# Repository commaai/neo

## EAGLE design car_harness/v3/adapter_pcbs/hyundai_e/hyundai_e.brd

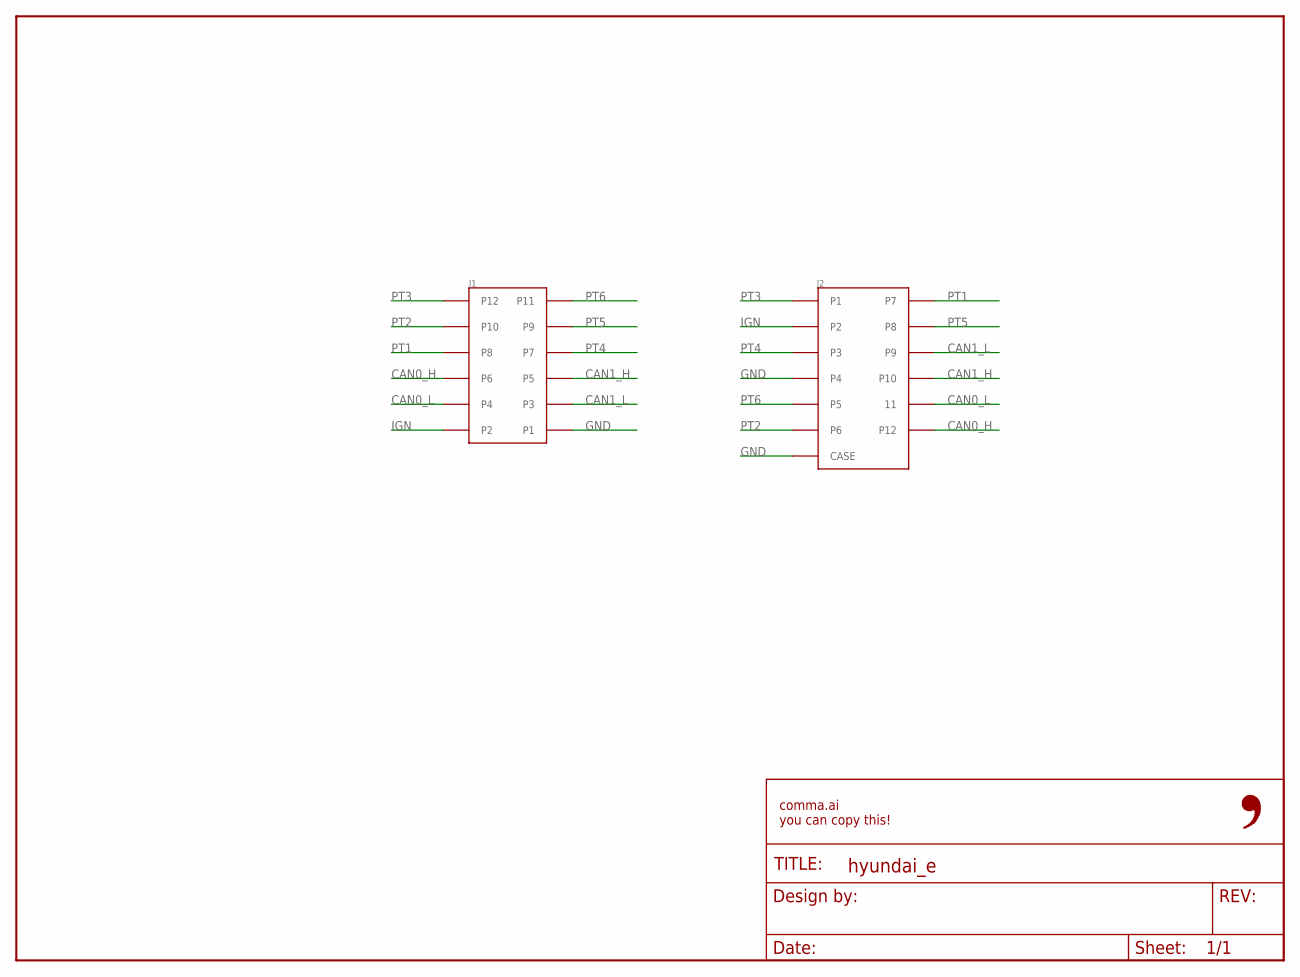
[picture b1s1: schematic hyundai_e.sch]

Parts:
FRAME1: FRAME-LETTER-OPENNO_PACKAGE; DUMMY
J1: 5018761240
J2: MG645845

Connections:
CAN0_H: J1.P6, J2.P12
CAN0_L: J1.P4, J2.P11 (11)
CAN1_H: J1.P5, J2.P10
CAN1_L: J1.P3, J2.P9
GND: J1.P1, J2.P4, J2.P$1 (CASE), J2.P$2 (CASE)
IGN: J1.P2, J2.P2
PT1: J1.P8, J2.P7
PT2: J1.P10, J2.P6
PT3: J1.P12, J2.P1
PT4: J1.P7, J2.P3
PT5: J1.P9, J2.P8
PT6: J1.P11, J2.P5

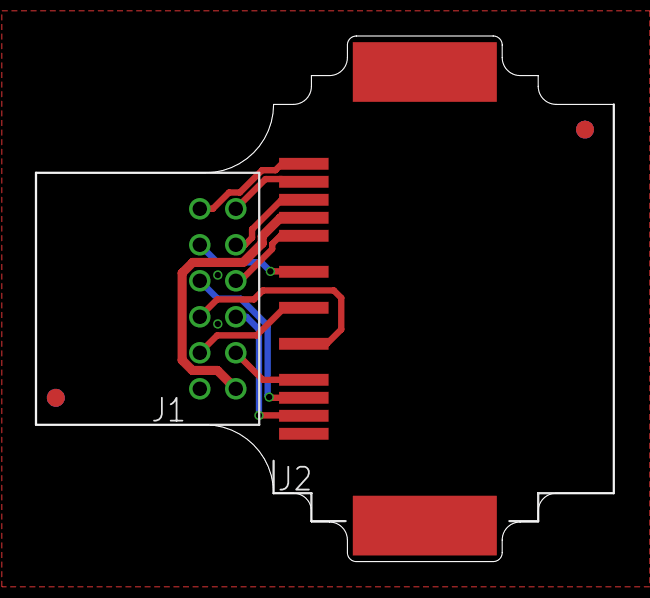
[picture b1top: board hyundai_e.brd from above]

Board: 2 copper layers, 32.1 x 29.2 mm, 6 parts (1 on the bottom side), 12 nets.

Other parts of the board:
U$1: LOGO
U$2, U$3: FIDUCIAL

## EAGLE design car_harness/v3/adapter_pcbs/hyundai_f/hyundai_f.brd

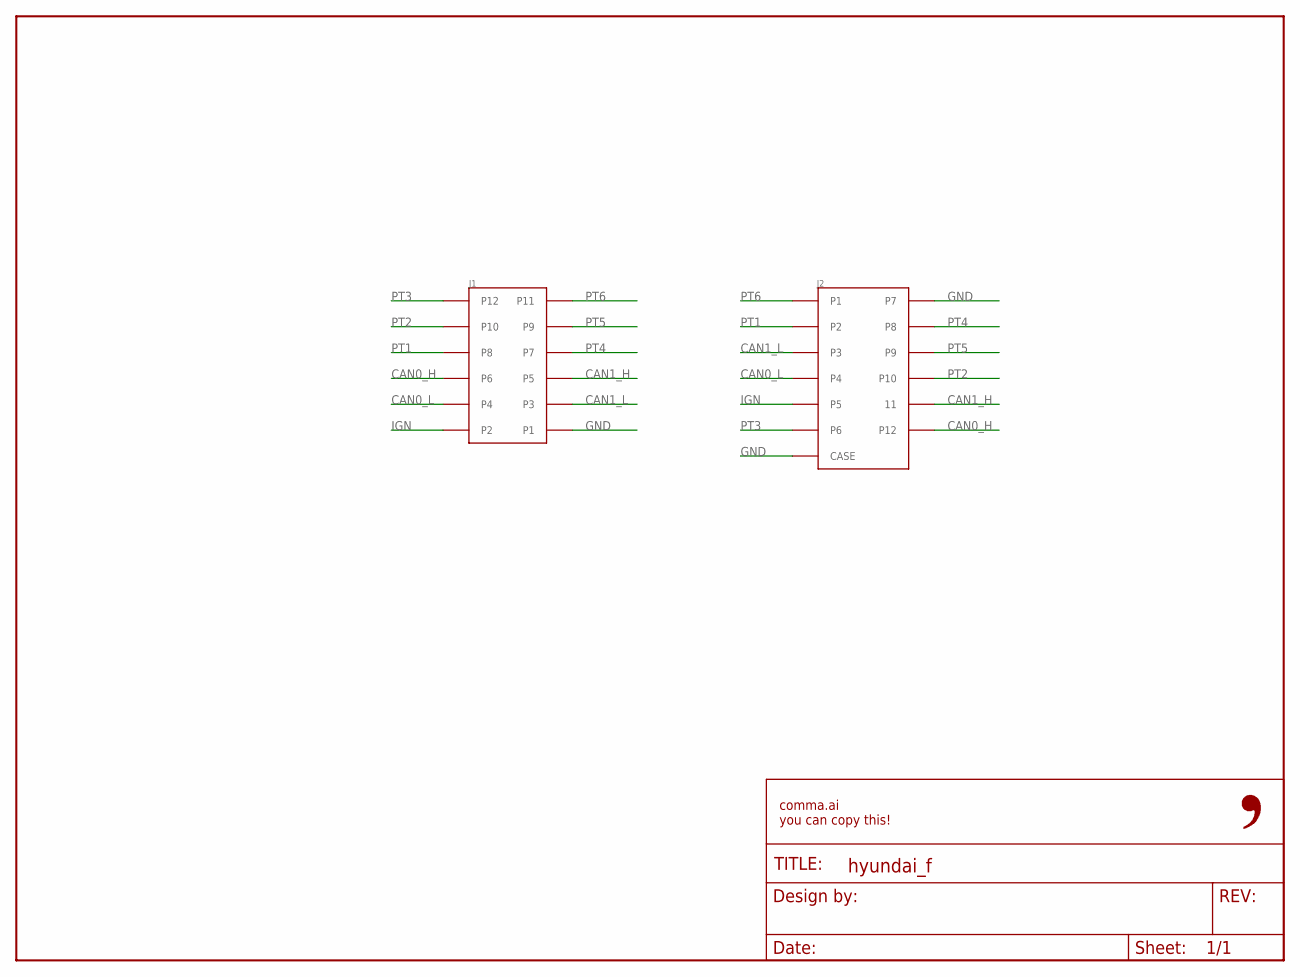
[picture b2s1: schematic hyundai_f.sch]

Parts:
FRAME1: FRAME-LETTER-OPENNO_PACKAGE; DUMMY
J1: 5018761240
J2: MG645845

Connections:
CAN0_H: J1.P6, J2.P12
CAN0_L: J1.P4, J2.P4
CAN1_H: J1.P5, J2.P11 (11)
CAN1_L: J1.P3, J2.P3
GND: J1.P1, J2.P7, J2.P$1 (CASE), J2.P$2 (CASE)
IGN: J1.P2, J2.P5
PT1: J1.P8, J2.P2
PT2: J1.P10, J2.P10
PT3: J1.P12, J2.P6
PT4: J1.P7, J2.P8
PT5: J1.P9, J2.P9
PT6: J1.P11, J2.P1

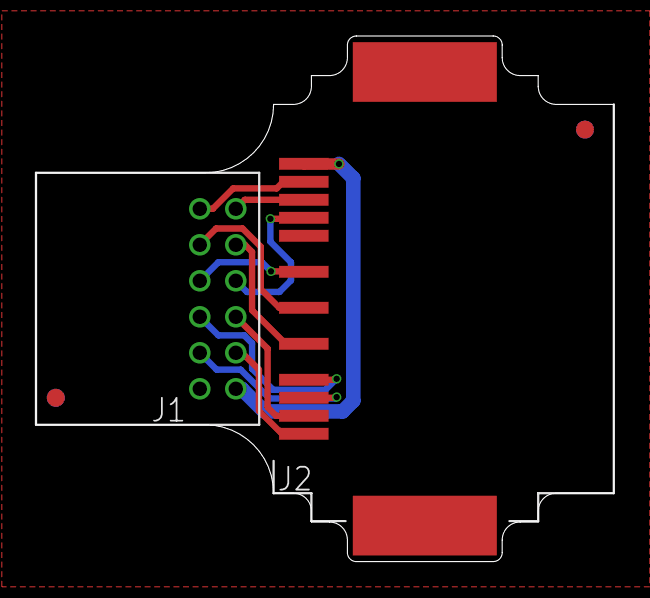
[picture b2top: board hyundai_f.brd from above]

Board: 2 copper layers, 32.1 x 29.2 mm, 6 parts (1 on the bottom side), 12 nets.

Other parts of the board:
U$1: LOGO
U$2, U$3: FIDUCIAL

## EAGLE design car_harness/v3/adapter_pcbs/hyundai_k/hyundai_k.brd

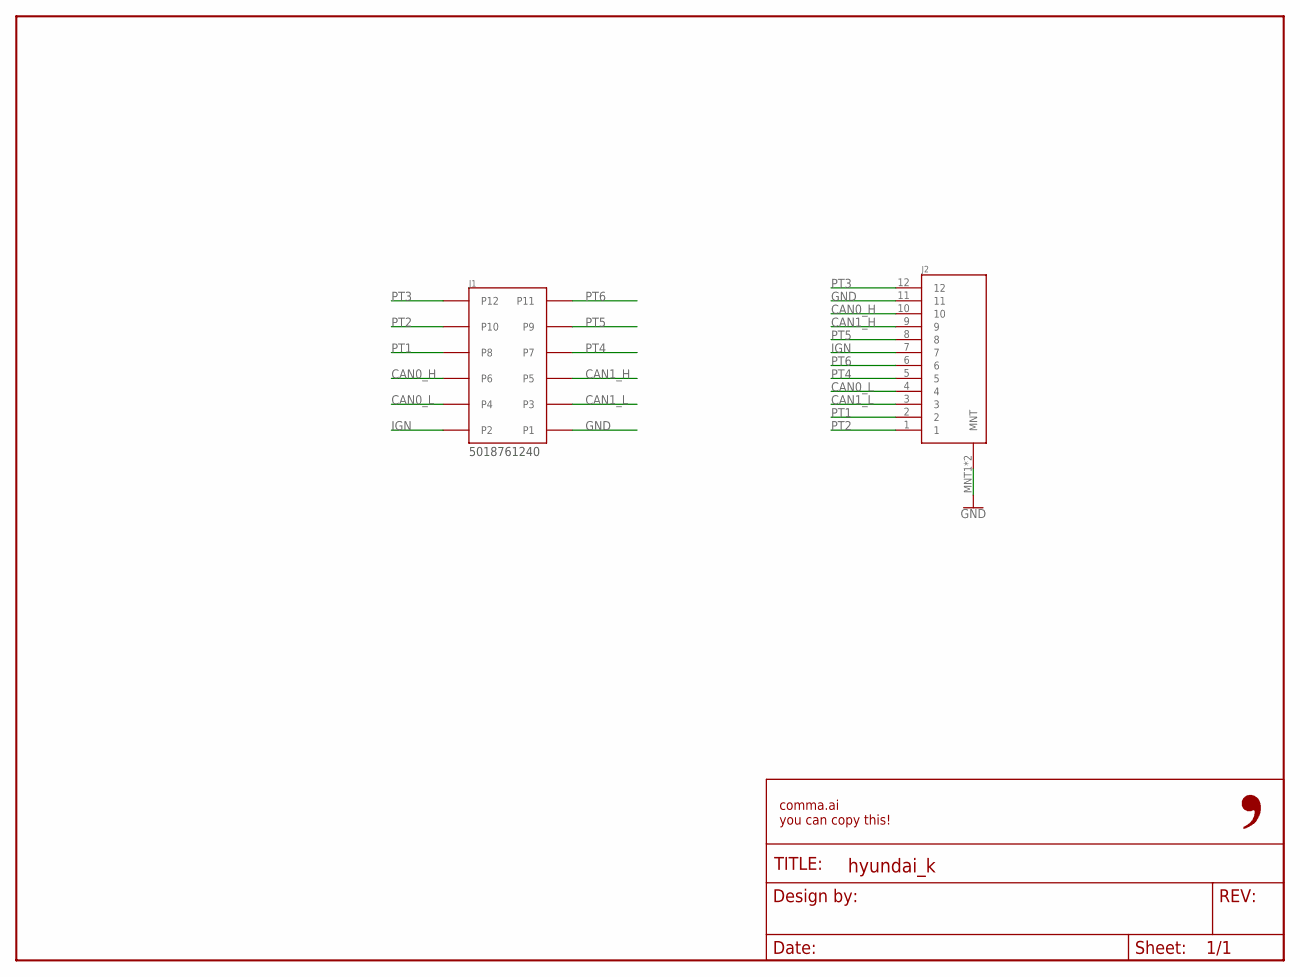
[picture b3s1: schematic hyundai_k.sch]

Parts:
FRAME1: FRAME-LETTER-OPENNO_PACKAGE; DUMMY
J1: 5018761240
J2: MG646151

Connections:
CAN0_H: J1.P6, J2.10
CAN0_L: J1.P4, J2.4
CAN1_H: J1.P5, J2.9
CAN1_L: J1.P3, J2.3
GND: J1.P1, J2.11, J2.MNT1 (MNT), J2.MNT2 (MNT)
IGN: J1.P2, J2.7
PT1: J1.P8, J2.2
PT2: J1.P10, J2.1
PT3: J1.P12, J2.12
PT4: J1.P7, J2.5
PT5: J1.P9, J2.8
PT6: J1.P11, J2.6

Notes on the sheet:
5018761240

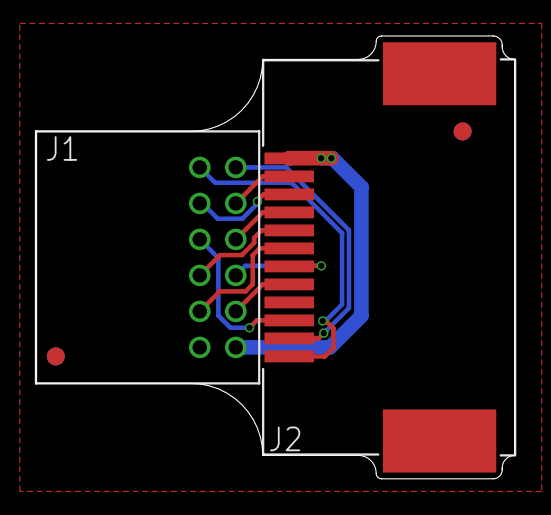
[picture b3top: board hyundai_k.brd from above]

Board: 2 copper layers, 26.6 x 24.6 mm, 6 parts (1 on the bottom side), 12 nets.

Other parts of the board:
U$1: LOGO
U$2, U$3: FIDUCIAL

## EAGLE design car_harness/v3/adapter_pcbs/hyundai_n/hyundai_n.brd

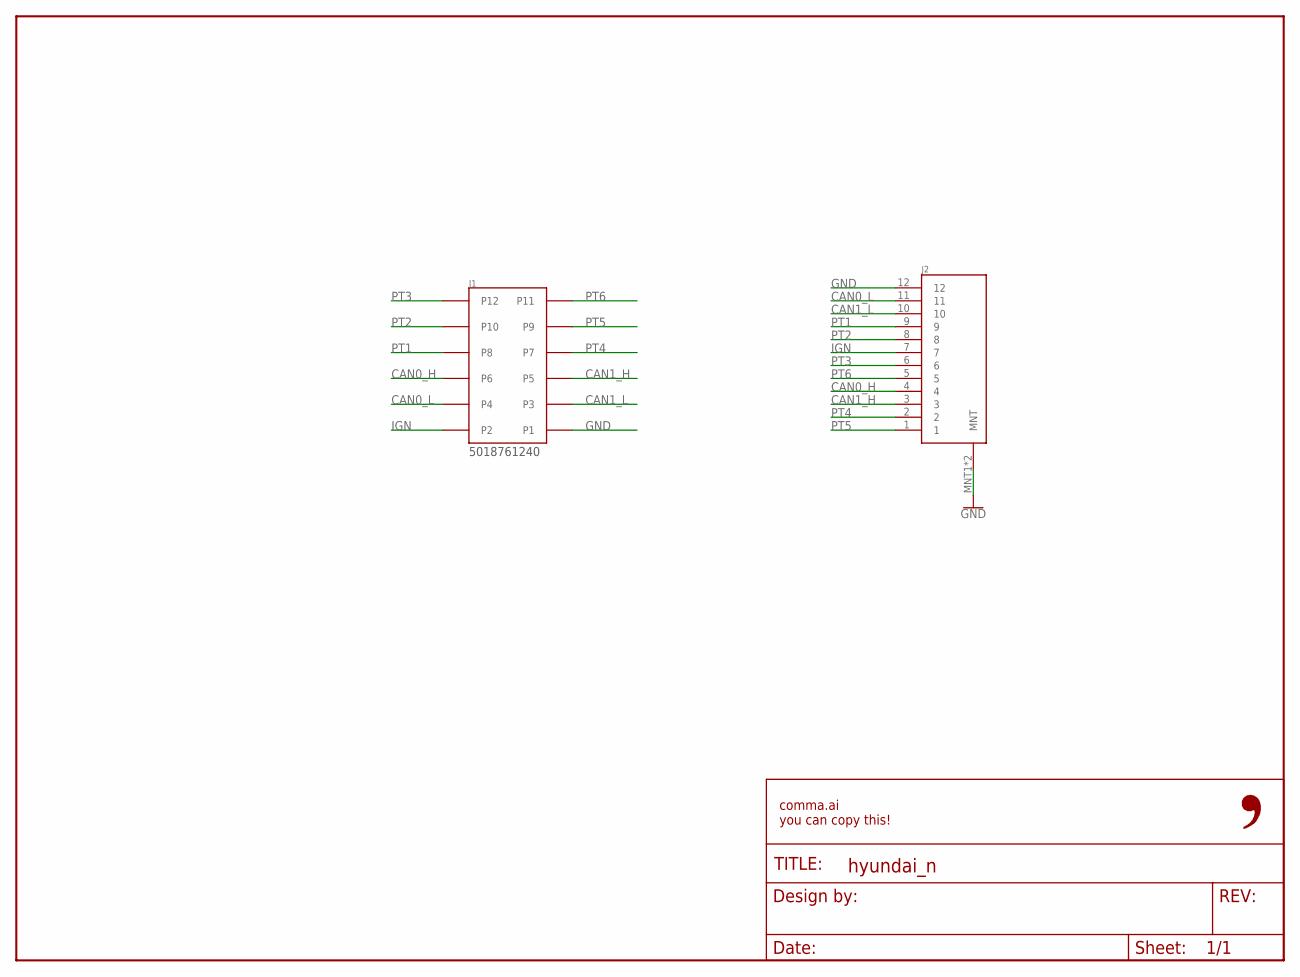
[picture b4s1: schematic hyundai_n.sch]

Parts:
FRAME1: FRAME-LETTER-OPENNO_PACKAGE; DUMMY
J1: 5018761240
J2: MG646151

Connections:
CAN0_H: J1.P6, J2.4
CAN0_L: J1.P4, J2.11
CAN1_H: J1.P5, J2.3
CAN1_L: J1.P3, J2.10
GND: J1.P1, J2.12, J2.MNT1 (MNT), J2.MNT2 (MNT)
IGN: J1.P2, J2.7
PT1: J1.P8, J2.9
PT2: J1.P10, J2.8
PT3: J1.P12, J2.6
PT4: J1.P7, J2.2
PT5: J1.P9, J2.1
PT6: J1.P11, J2.5

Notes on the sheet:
5018761240

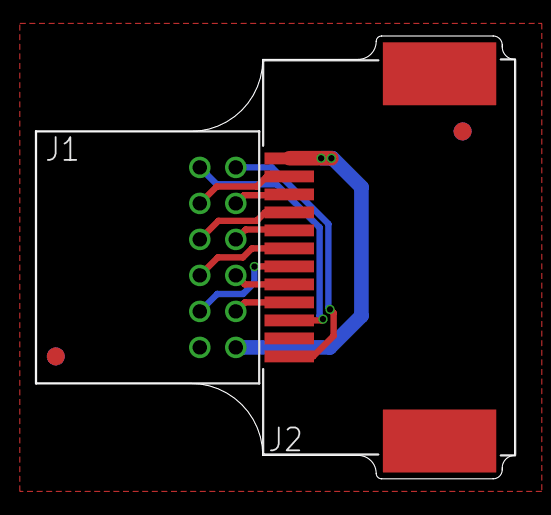
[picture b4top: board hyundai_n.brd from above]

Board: 2 copper layers, 26.6 x 24.6 mm, 6 parts (1 on the bottom side), 12 nets.

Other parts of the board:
U$1: LOGO
U$2, U$3: FIDUCIAL
